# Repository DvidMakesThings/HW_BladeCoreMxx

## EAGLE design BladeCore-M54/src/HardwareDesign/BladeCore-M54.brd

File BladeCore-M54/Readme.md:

# BladeCore-M54

BladeCore-M54 is a versatile 6-layer embedded system module built around the RP2040 microcontroller, designed for modularity and high-speed experimentation in constrained spaces.  
It uses an M.2 form factor and includes a carefully routed, length-matched 16MB QSPI flash capable of operating at full 133 MHz quad I/O speeds — theoretically up to 532 Mbps effective throughput.  

The module provides optional breakouts for ADC, I²C, UART, GPIO, and USB signals — configurable based on application needs. Core voltage is externally adjustable via a trimpot-controlled LDO (AP7335-WG-7), enabling safe overclocking without risk of oversupply.  

USB routing is dynamically switchable using the PI3USB102J, allowing the single USB-C port to connect either to the MCU or to an FT232RNQ interface for debug automation.  
Boot/reset are handled programmatically; no physical boot/reset buttons are needed.  

It also includes:
- a high-precision 3.0 V analog reference supply (AVDD),
- a unique-ID EEPROM for per-module identification,
- and default configurations that favor RP2040-based development while leaving everything else adaptable.

BladeCore-M54 is not locked into any specific use case — it is meant to be reconfigured as needed.

---

## Highlights

- **RP2040 MCU** with external core voltage supply (AP7335-WG-7) for **safe overclocking** via trimpot  
- **16MB W25Q128JV QSPI Flash**, length-matched for up to **133 MHz quad I/O** (532 Mbps effective transfer rate)  
- **PI3USB102J USB switch**: 1 USB-C can switch between MCU and FT232RNQ (auto-debug, single cable)  
- Optional ADC, I²C, UART, and GPIO breakouts — **use what you need**  
- **No physical reset/boot buttons** — fully controllable by firmware  
- **3.0 V precision AVDD** generator for analog use  
- **External EEPROM with unique ID**  
- **Custom 6-layer JLC stackup**, tuned for signal integrity  
- **DMT signature layout** with aggressive routing and style

---

## Stackup

**JLC06081H-2116 (Finished Thickness: ~0.83 mm ±0.10 mm) – 6 Layers**

- Total Layers: 6  
- Finished Thickness: ~0.83 mm (±0.10 mm)  
- Outer Copper Weight: 1 oz  
- Inner Copper Weight: 0.5 oz  
- Prepreg & Core Materials: FR4 (JLC06081H-2116)

| Layer | Description     | Material                      | Thickness (mm) |
|-------|------------------|-------------------------------|----------------|
| L1    | Signal (Top)     | Outer Copper 1 oz             | 0.0350         |
|       | Prepreg          | 2116 RC54%, 4.9mil            | 0.1164         |
| L2    | Ground Plane     | Inner Copper 0.5 oz           | 0.0152         |
|       | Core             | 0.13 mm HOZ without copper    | 0.1300         |
| L3    | Power Plane      | Inner Copper 0.5 oz           | 0.0152         |
|       | Prepreg          | 7628 RC49%, 8.6mil            | 0.2028         |
| L4    | Signal           | Inner Copper 0.5 oz           | 0.0152         |
|       | Core             | 0.13 mm HOZ without copper    | 0.1300         |
| L5    | Ground Plane     | Inner Copper 0.5 oz           | 0.0152         |
|       | Prepreg          | 2116 RC54%, 4.9mil            | 0.1164         |
| L6    | Signal (Bottom)  | Outer Copper 1 oz             | 0.0350         |
|       |                  | **Total Thickness**           | **0.8304 mm**  |

---

## Pinout

| Pin | Signal      | Direction | Description |
|-----|-------------|-----------|-------------|
| 1   | GP15        | I/O       |             |
| 2   | GP29        | I/O       | ADC Channel 3 |
| 3   | GP14        | I/O       |             |
| 4   | GP28        | I/O       | ADC Channel 2 |
| 5   | GP13        | I/O       |             |
| 6   | GP27        | I/O       | ADC Channel 1 |
| 7   | GP12        | I/O       |             |
| 8   | GP26        | I/O       | ADC Channel 0 |
| 9   | GP11        | I/O       |             |
| 10  | GP25        | I/O       | USB MUX Select. For normal functionality, remove M1 and populate M3 (RP2040 USB) or M2 (FT232 USB). Default: M1 = 0Ω, M3 = 10K, M2 = DNI. |
| 11  | GP10        | I/O       |             |
| 12  | GP24        | I/O       |             |
| 13  | GP9         | I/O       | UART1 RX. Connected to FT232 via R01 (DNI). |
| 14  | GP23        | I/O       |             |
| 15  | GP8         | I/O       | UART1 TX. Connected to FT232 via T11 (DNI). |
| 16  | GP22        | I/O       |             |
| 17  | GP7         | I/O       |             |
| 18  | GP21        | I/O       |             |
| 19  | GP6         | I/O       |             |
| 20  | GP20        | I/O       |             |
| 21  | GP5         | I/O       | I2C0 SCL. Pulled high via R23 (3.3K). Remove R3 (0Ω) for non-I2C use. |
| 22  | GP19        | I/O       |             |
| 23  | GP4         | I/O       | I2C0 SDA. Pulled high via R24 (3.3K). Remove R4 (0Ω) for non-I2C use. |
| 24  | GP18        | I/O       |             |
| 25  | GP3         | I/O       |             |
| 26  | GP17        | I/O       |             |
| 27  | GP2         | I/O       |             |
| 28  | GP16        | I/O       |             |
| 29  | GP1         | I/O       | UART0 RX. Connected to FT232 via M1 (0Ω). |
| 30  | GND         | —         |             |
| 31  | GP0         | I/O       | UART0 TX. Connected to FT232 via T01 (0Ω). |
| 32  | NC          | —         | No functionality, used by BladeCore-M54. |
| 33  | GND         | —         |             |
| 34  | NC          | —         | No functionality, used by BladeCore-M54. |
| 35  | NC          | —         | No functionality, used by BladeCore-M54. |
| 36  | NC          | —         | No functionality, used by BladeCore-M54. |
| 37  | NC          | —         | No functionality, used by BladeCore-M54. |
| 38  | NC          | —         | No functionality, used by BladeCore-M54. |
| 39  | NC          | —         | No functionality, used by BladeCore-M54. |
| 40  | NC          | —         | No functionality, used by BladeCore-M54. |
| 41  | NC          | —         | No functionality, used by BladeCore-M54. |
| 42  | NC          | —         | No functionality, used by BladeCore-M54. |
| 43  | NC          | —         | No functionality, used by BladeCore-M54. |
| 44  | NC          | —         | No functionality, used by BladeCore-M54. |
| 45  | NC          | —         | No functionality, used by BladeCore-M54. |
| 46  | NC          | —         | No functionality, used by BladeCore-M54. |
| 47  | NC          | —         | No functionality, used by BladeCore-M54. |
| 48  | NC          | —         | No functionality, used by BladeCore-M54. |
| 49  | NC          | —         | No functionality, used by BladeCore-M54. |
| 50  | NC          | —         | No functionality, used by BladeCore-M54. |
| 51  | GND         | —         | System ground |
| 52  | GND         | —         | System ground |
| 53  | USB D+      | I/O       |             |
| 54  | RESET       | Input     |             |
| 55  | USB D-      | I/O       |             |
| 56  | SWDIO       | I/O       |             |
| 57  | DETECT      | -         | Pull low externally |
| 58  | SWCLK       | Input     |             |
| 67  | +3.3V       | PWR       | RP2040 supply voltage. Max 3.6V, typical 3.3V. |
| 68  | +3.3V       | PWR       |             |
| 69  | +3.3V       | PWR       |             |
| 70  | GND         | —         | System ground |
| 71  | GND         | —         | System ground |
| 72  | GND         | —         | System ground |
| 73  | VBUS        | PWR IN    | External power input. Max 5.5V. |
| 74  | VBUS        | PWR IN    | External power input. Max 5.5V. |
| 75  | VBUS        | PWR IN    | External power input. Max 5.5V. |

## Misc: Core Voltage & Overclocking

To overclock the MCU, it's possible to supply more than 1.1 V to the core.  
By default, **external core voltage generation** is enabled using the **AP7335-WG-7**, which is activated via **J1**.  
The output voltage is set by adjusting the **R1 trimpot**.

> ⚠️ It is safe — the voltage range is limited by design and cannot damage the MCU.

### Voltage Range (Set by Divider)

| R1 (Trimpot) | Total Resistance (R28 + R1) | VOUT (approx) |
|--------------|----------------------------|----------------|
| 25 kΩ (max)  | 47 kΩ                       | 1.02 V         |
| 12.5 kΩ      | 34.5 kΩ                     | 1.14 V         |
| 0 Ω (min)    | 22 kΩ                       | 1.22 V         |

### Use Cases

- **Low Power Mode:** R1 = 25 kΩ → ~1.02 V  
- **Default / Safe:** R1 = 12.5 kΩ → ~1.14 V  
- **High Performance / Overclocking:** R1 = 0 Ω → ~1.22 V  

### VOUT Behavior Across Temperatures and Trim Settings

The AP7335-WG-7 regulator is affected by temperature-dependent reference voltage (VREF), output voltage accuracy, and resistor tolerances.  
This section outlines the **worst-case VOUT values** at cold, normal, and hot temperatures, across all trimpot settings.

> ⚙️ **Calculation Parameters:**
> - VOUT Accuracy: ±2% (from AP7335-WG-7 datasheet)
> - VREF Variation: Based on VREF vs. Temperature graph  
>   - −50 °C → 0.89 V  
>   - 25 °C → 0.80 V  
>   - 125 °C → 0.782 V
> - Resistors used: 1% tolerance (R27 = 12 kΩ, R28 = 22 kΩ, R1 = 0–25 kΩ trimpot)

The RP2040's **absolute maximum core voltage is 1.3 V** — values exceeding this may cause damage.

---

### ❄️ Cold (–50 °C, VREF = 0.89 V)

**Max Trim (R1 = 25 kΩ, Rb = 47 kΩ)**  
VOUT: **1.090 V – 1.144 V** ✅ Safe

**Mid Trim (R1 = 12.5 kΩ, Rb = 34.5 kΩ)**  
VOUT: **1.170 V – 1.230 V** ✅ Safe

**Min Trim (R1 = 0 Ω, Rb = 22 kΩ)**  
VOUT: **1.339 V – 1.413 V** ❌ Danger – exceeds RP2040 1.3 V limit

---

### 🌤️ Normal (25 °C, VREF = 0.80 V)

**Max Trim (R1 = 25 kΩ, Rb = 47 kΩ)**  
VOUT: **0.980 V – 1.029 V** ✅ Safe

**Mid Trim (R1 = 12.5 kΩ, Rb = 34.5 kΩ)**  
VOUT: **1.051 V – 1.106 V** ✅ Safe

**Min Trim (R1 = 0 Ω, Rb = 22 kΩ)**  
VOUT: **1.201 V – 1.265 V** ✅ Safe

---

### 🔥 Hot (125 °C, VREF = 0.782 V)

**Max Trim (R1 = 25 kΩ, Rb = 47 kΩ)**  
VOUT: **0.958 V – 1.005 V** ✅ Safe

**Mid Trim (R1 = 12.5 kΩ, Rb = 34.5 kΩ)**  
VOUT: **1.028 V – 1.082 V** ✅ Safe

**Min Trim (R1 = 0 Ω, Rb = 22 kΩ)**  
VOUT: **1.180 V – 1.243 V** ✅ Safe

### Switching to Internal Core LDO

To use the **internally generated core voltage** (from RP2040's internal LDO):

1. Move **J1 → J2**  
2. Populate **J3** with a 0 Ω jumper  

**Default configuration:**
- J1 = 10 kΩ  
- J2 = DNI  
- J3 = DNI

---
## License
This project is licensed under the GPL-3.0 License. See the [LICENSE](LICENSE) file for details.

## Contact
For questions or feedback:
- Email: [dvidmakesthing@gmail.com](mailto:dvidmakesthing@gmail.com)
- GitHub: [DvidMakesThings](https://github.com/DvidMakesThings)

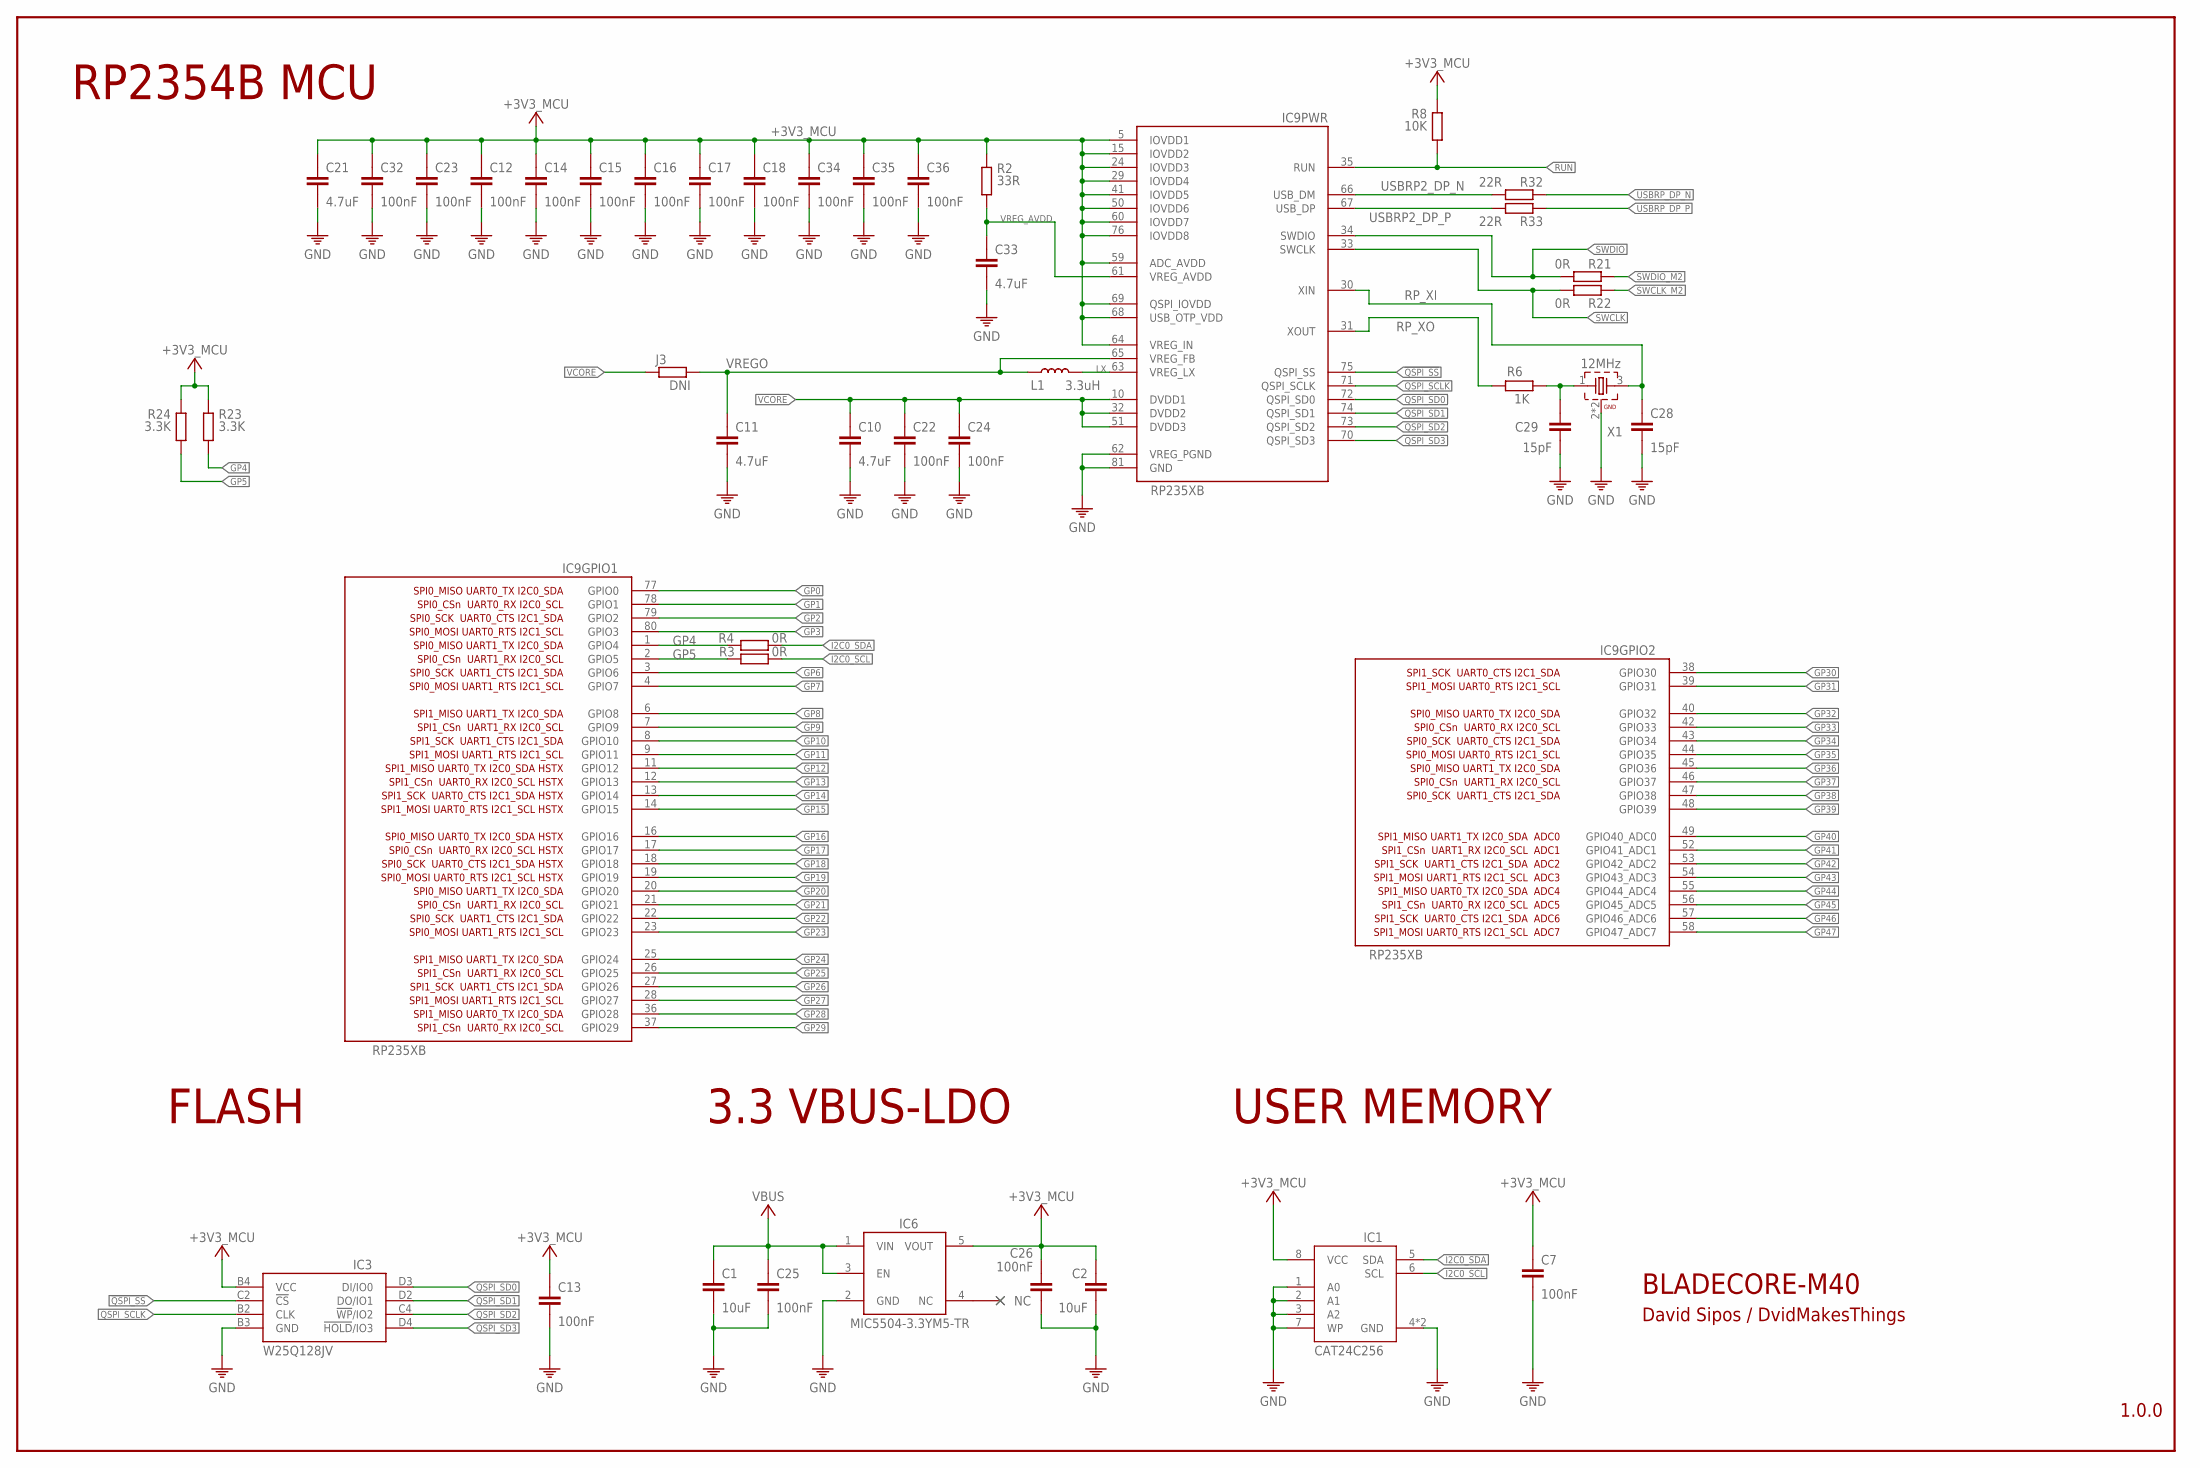
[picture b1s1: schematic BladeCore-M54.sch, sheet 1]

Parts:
C1, C2: 10uF; 0805
C7, C12, C13, C14, C15, C16, C17, C18, C22, C23, C24, C25, C26, C32, C34, C35, C36: 100nF; 0201
C10, C11, C33: 4.7uF; 0201
C21: 4.7uF; C0402
C28, C29: 15pF; 0201
IC1: CAT24C512HU5IGT3; SON50P300X200X50-9T130X140N
IC3: W25Q128JVCIQ TR; BGA24C100P4X6_800X600X120N
IC6: MIC5504-3.3YM5-TR; SOT23-5
IC9: RP235XB; QFN80-10X10
J3: DNI; R0201
L1: 3.3uH; SRR5228A
R2: 33R; R0201
R3, R4, R21, R22: 0R; R0201
R6: 1K; R0201
R8: 10K; R0201
R23, R24: 3.3K; R0201
R32, R33: 22R; R0201
X1: 12MHz; WE-XTAL_CFPX-180

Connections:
!QSPI_SS: IC3.C2 (!CS), IC9.75 (QSPI_SS)
+3V3_MCU: C2.1, C7.1, C12.1, C13.1, C14.1, C15.1, C16.1, C17.1, C18.1, C21.1, C23.1, C26.1, C32.1, C34.1, C35.1, C36.1, IC1.8 (VCC), IC3.B4 (VCC), IC6.5 (VOUT), IC9.5 (IOVDD1), IC9.15 (IOVDD2), IC9.24 (IOVDD3), IC9.29 (IOVDD4), IC9.41 (IOVDD5), IC9.50 (IOVDD6), IC9.59 (ADC_AVDD), IC9.60 (IOVDD7), IC9.64 (VREG_IN), IC9.68 (USB_OTP_VDD), IC9.69 (QSPI_IOVDD), IC9.76 (IOVDD8), R2.1, R8.1, R23.1, R24.1; also elsewhere on the board
GND: C1.2, C2.2, C7.2, C10.2, C11.2, C12.2, C13.2, C14.2, C15.2, C16.2, C17.2, C18.2, C21.2, C22.2, C23.2, C24.2, C25.2, C26.2, C28.2, C29.2, C32.2, C33.2, C34.2, C35.2, C36.2, IC1.1 (A0), IC1.2 (A1), IC1.3 (A2), IC1.4 (GND), IC1.7 (WP), IC1.9 (GND), IC3.B3 (GND), IC6.2 (GND), IC9.62 (VREG_PGND), IC9.81 (GND), X1.2 (GND), X1.4 (GND); also elsewhere on the board
GP0: IC9.77 (GPIO0); also elsewhere on the board
GP1: IC9.78 (GPIO1); also elsewhere on the board
GP2: IC9.79 (GPIO2); also elsewhere on the board
GP3: IC9.80 (GPIO3); also elsewhere on the board
GP4: IC9.1 (GPIO4), R4.1, R23.2; also elsewhere on the board
GP5: IC9.2 (GPIO5), R3.1, R24.2; also elsewhere on the board
GP6: IC9.3 (GPIO6); also elsewhere on the board
GP7: IC9.4 (GPIO7); also elsewhere on the board
GP8: IC9.6 (GPIO8); also elsewhere on the board
GP9: IC9.7 (GPIO9); also elsewhere on the board
GP10: IC9.8 (GPIO10); also elsewhere on the board
GP11: IC9.9 (GPIO11); also elsewhere on the board
GP12: IC9.11 (GPIO12); also elsewhere on the board
GP13: IC9.12 (GPIO13); also elsewhere on the board
GP14: IC9.13 (GPIO14); also elsewhere on the board
GP15: IC9.14 (GPIO15); also elsewhere on the board
GP16: IC9.16 (GPIO16); also elsewhere on the board
GP17: IC9.17 (GPIO17); also elsewhere on the board
GP18: IC9.18 (GPIO18); also elsewhere on the board
GP19: IC9.19 (GPIO19); also elsewhere on the board
GP20: IC9.20 (GPIO20); also elsewhere on the board
GP21: IC9.21 (GPIO21); also elsewhere on the board
GP22: IC9.22 (GPIO22); also elsewhere on the board
GP23: IC9.23 (GPIO23); also elsewhere on the board
GP24: IC9.25 (GPIO24); also elsewhere on the board
GP25: IC9.26 (GPIO25); also elsewhere on the board
GP26: IC9.27 (GPIO26); also elsewhere on the board
GP27: IC9.28 (GPIO27); also elsewhere on the board
GP28: IC9.36 (GPIO28); also elsewhere on the board
GP29: IC9.37 (GPIO29); also elsewhere on the board
GP30: IC9.38 (GPIO30); also elsewhere on the board
GP31: IC9.39 (GPIO31); also elsewhere on the board
GP32: IC9.40 (GPIO32); also elsewhere on the board
GP33: IC9.42 (GPIO33); also elsewhere on the board
GP34: IC9.43 (GPIO34); also elsewhere on the board
GP35: IC9.44 (GPIO35); also elsewhere on the board
GP36: IC9.45 (GPIO36); also elsewhere on the board
GP37: IC9.46 (GPIO37); also elsewhere on the board
GP38: IC9.47 (GPIO38); also elsewhere on the board
GP39: IC9.48 (GPIO39); also elsewhere on the board
GP40: IC9.49 (GPIO40_ADC0); also elsewhere on the board
GP41: IC9.52 (GPIO41_ADC1); also elsewhere on the board
GP42: IC9.53 (GPIO42_ADC2); also elsewhere on the board
GP43: IC9.54 (GPIO43_ADC3); also elsewhere on the board
GP44: IC9.55 (GPIO44_ADC4); also elsewhere on the board
GP45: IC9.56 (GPIO45_ADC5); also elsewhere on the board
GP46: IC9.57 (GPIO46_ADC6); also elsewhere on the board
GP47: IC9.58 (GPIO47_ADC7); also elsewhere on the board
I2C0_SCL: IC1.6 (SCL), R3.2
I2C0_SDA: IC1.5 (SDA), R4.2
LX: IC9.63 (VREG_LX), L1.2
unnamed: C29.1, R6.1, X1.1
QSPI_SCLK: IC3.B2 (CLK), IC9.71 (QSPI_SCLK)
QSPI_SD0: IC3.D3 (DI/IO0), IC9.72 (QSPI_SD0)
QSPI_SD1: IC3.D2 (DO/IO1), IC9.74 (QSPI_SD1)
QSPI_SD2: IC3.C4 (!WP!/IO2), IC9.73 (QSPI_SD2)
QSPI_SD3: IC3.D4 (!HOLD!/IO3), IC9.70 (QSPI_SD3)
RP_XI: C28.1, IC9.30 (XIN), X1.3 (2)
RP_XO: IC9.31 (XOUT), R6.2
RUN: IC9.35 (RUN), R8.2; also elsewhere on the board
SWCLK: IC9.33 (SWCLK), R22.2
SWCLK_M2: R22.1; also elsewhere on the board
SWDIO: IC9.34 (SWDIO), R21.2
SWDIO_M2: R21.1; also elsewhere on the board
USBRP2_DP_N: IC9.66 (USB_DM), R32.2
USBRP2_DP_P: IC9.67 (USB_DP), R33.2
USBRP_DP_N: R32.1; also elsewhere on the board
USBRP_DP_P: R33.1; also elsewhere on the board
VBUS: C1.1, C25.1, IC6.1 (VIN), IC6.3 (EN); also elsewhere on the board
VCORE: C10.1, C22.1, C24.1, IC9.10 (DVDD1), IC9.32 (DVDD2), IC9.51 (DVDD3), J3.2
VREGO: C11.1, IC9.65 (VREG_FB), J3.1, L1.1
VREG_AVDD: C33.1, IC9.61 (VREG_AVDD), R2.2

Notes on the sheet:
RP2354B MCU
BLADECORE-M40
1.0.0
David Sipos / DvidMakesThings
3.3 VBUS-LDO
FLASH
USER MEMORY

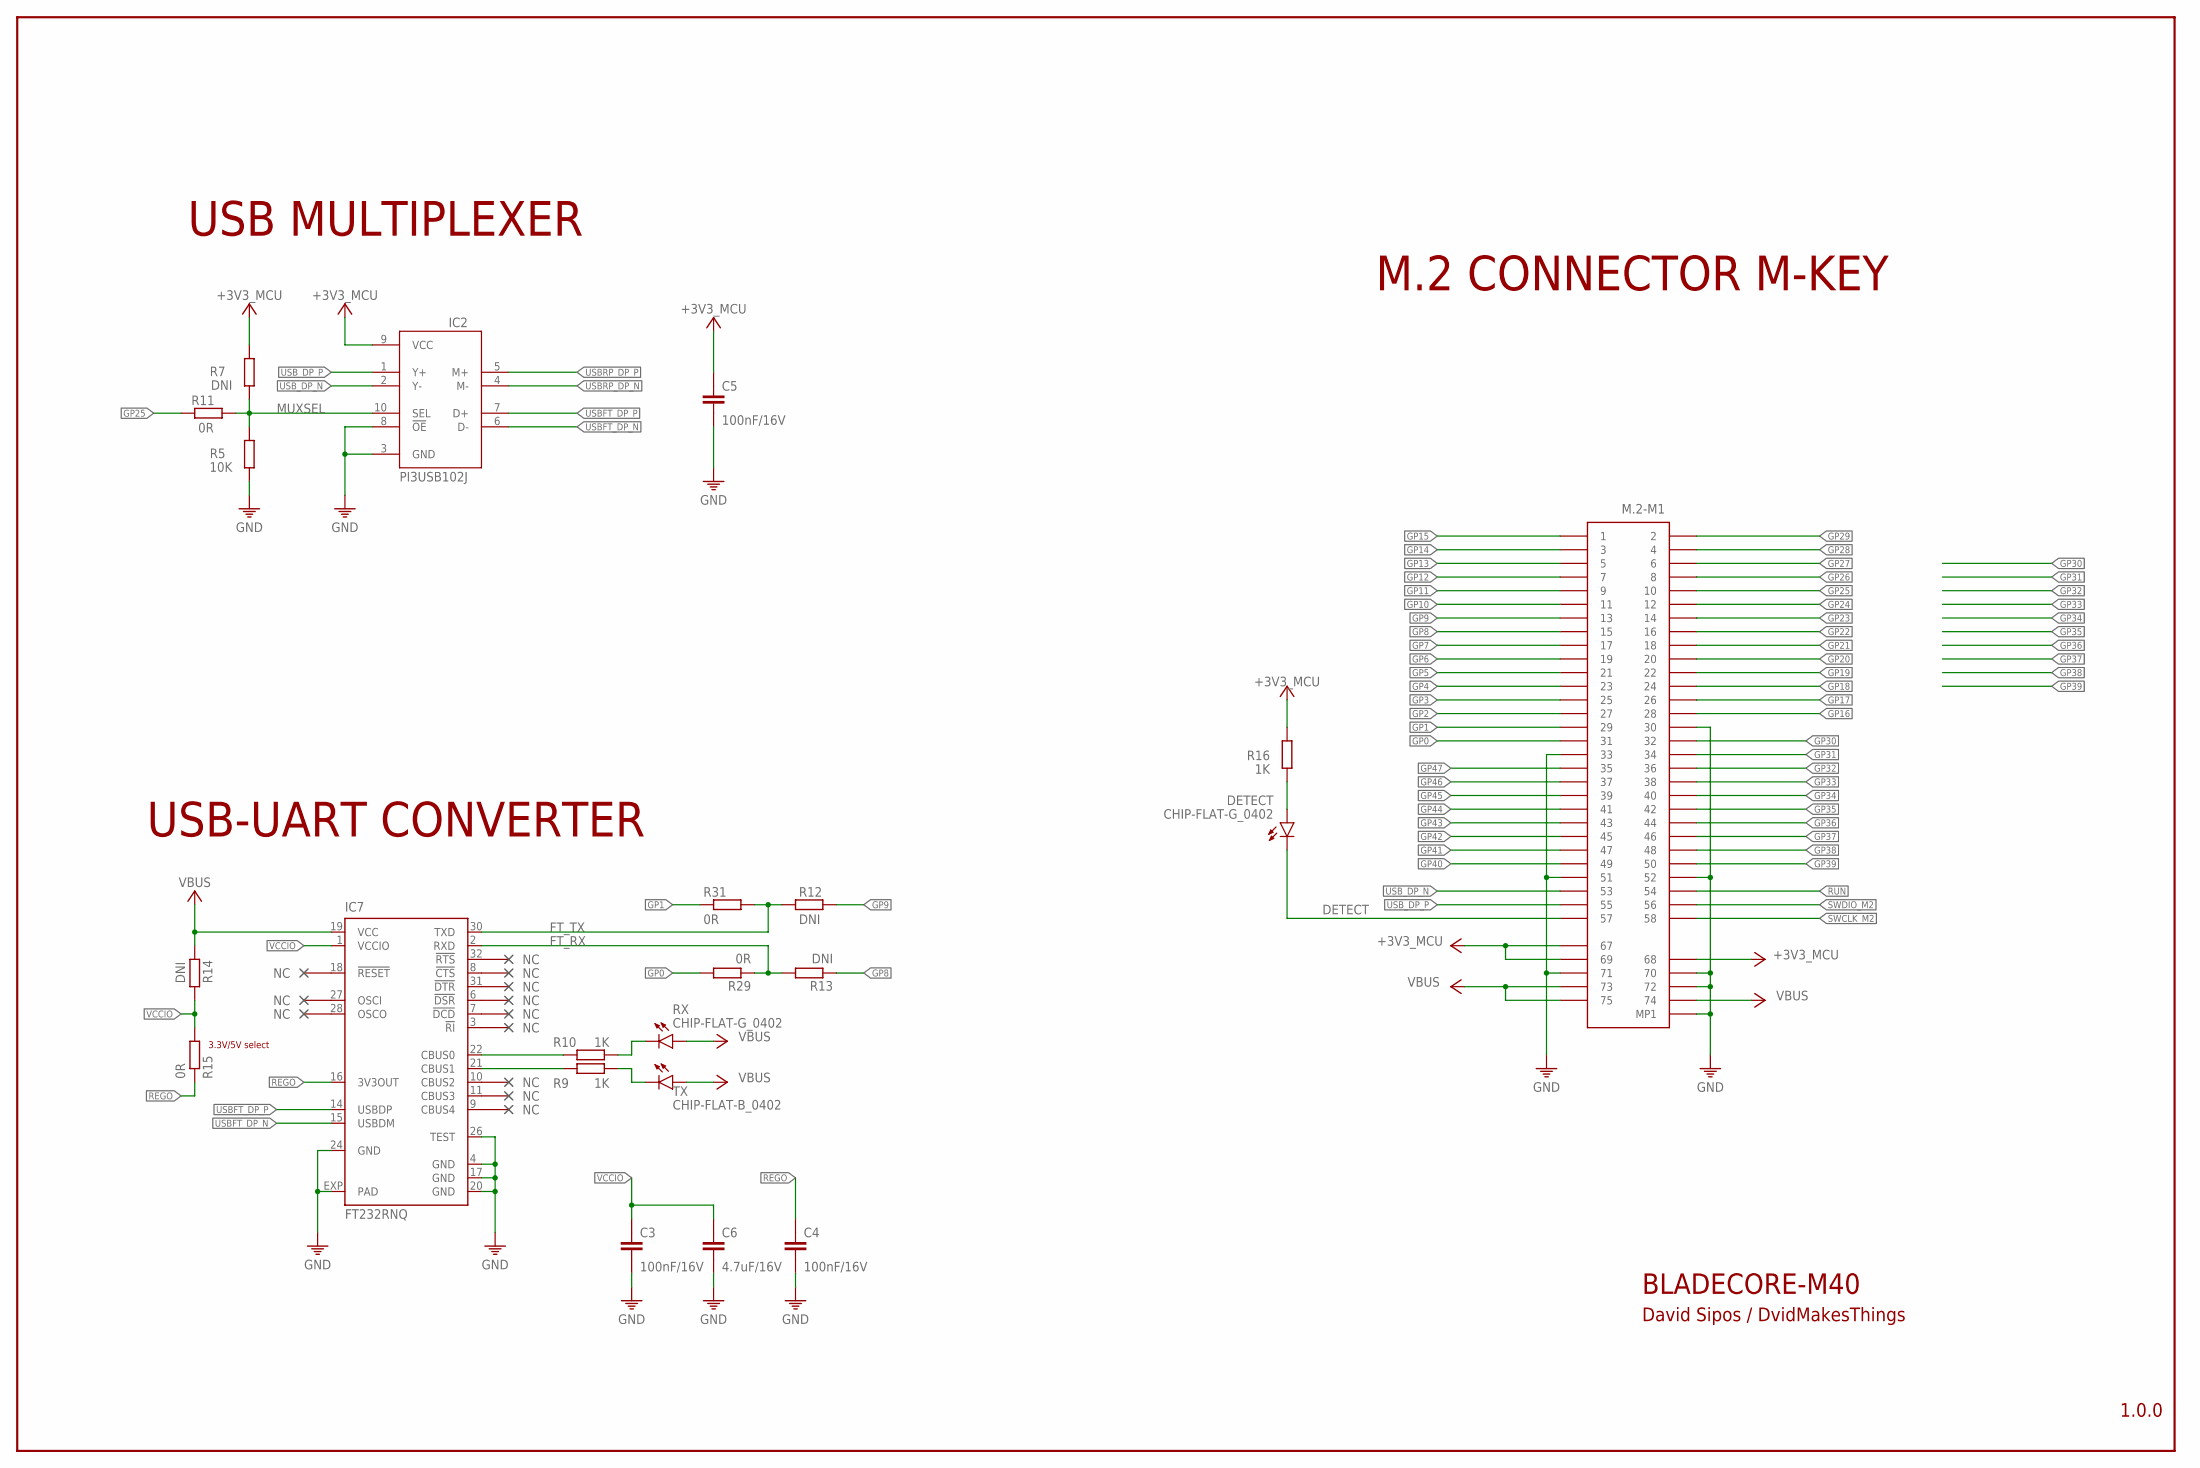
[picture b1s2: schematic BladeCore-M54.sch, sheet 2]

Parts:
C3, C4, C5: 100nF/16V; 0201
C6: 4.7uF/16V; 0201
DETECT: CHIP-FLAT-G_0402; LEDC1005X25N_FLAT-G
IC2: PI3USB102J; QFN40P120X140X35-10N
IC7: FT232RNQ; QFN32
M.2-M1: M.2-M-KEY
R5: 10K; R0201
R7, R12, R13, R14: DNI; R0201
R9, R10, R16: 1K; R0201
R11, R15, R29, R31: 0R; R0201
RX: CHIP-FLAT-G_0402; LEDC1005X25N_FLAT-G
TX: CHIP-FLAT-B_0402; LEDC1005X25N_FLAT-B

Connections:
+3V3_MCU: C5.1, IC2.9 (VCC), M.2-M1.P$67 (67), M.2-M1.P$68 (68), M.2-M1.P$69 (69), R7.2, R16.2; also elsewhere on the board
DETECT: DETECT.C, M.2-M1.P$57 (57)
FT_RX: IC7.2 (RXD), R13.2, R29.1
FT_TX: IC7.30 (TXD), R12.1, R31.2
GND: C3.2, C4.2, C5.2, C6.2, IC2.3 (GND), IC2.8 (!OE), IC7.4 (GND), IC7.17 (GND), IC7.20 (GND), IC7.24 (GND), IC7.26 (TEST), IC7.EXP (PAD), M.2-M1.MT1 (MP1), M.2-M1.P$30 (30), M.2-M1.P$33 (33), M.2-M1.P$51 (51), M.2-M1.P$52 (52), M.2-M1.P$70 (70), M.2-M1.P$71 (71), M.2-M1.P$72 (72), R5.1; also elsewhere on the board
GP0: M.2-M1.P$31 (31), R29.2; also elsewhere on the board
GP1: M.2-M1.P$29 (29), R31.1; also elsewhere on the board
GP2: M.2-M1.P$27 (27); also elsewhere on the board
GP3: M.2-M1.P$25 (25); also elsewhere on the board
GP4: M.2-M1.P$23 (23); also elsewhere on the board
GP5: M.2-M1.P$21 (21); also elsewhere on the board
GP6: M.2-M1.P$19 (19); also elsewhere on the board
GP7: M.2-M1.P$17 (17); also elsewhere on the board
GP8: M.2-M1.P$15 (15), R13.1; also elsewhere on the board
GP9: M.2-M1.P$13 (13), R12.2; also elsewhere on the board
GP10: M.2-M1.P$11 (11); also elsewhere on the board
GP11: M.2-M1.P$9 (9); also elsewhere on the board
GP12: M.2-M1.P$7 (7); also elsewhere on the board
GP13: M.2-M1.P$5 (5); also elsewhere on the board
GP14: M.2-M1.P$3 (3); also elsewhere on the board
GP15: M.2-M1.P$1 (1); also elsewhere on the board
GP16: M.2-M1.P$28 (28); also elsewhere on the board
GP17: M.2-M1.P$26 (26); also elsewhere on the board
GP18: M.2-M1.P$24 (24); also elsewhere on the board
GP19: M.2-M1.P$22 (22); also elsewhere on the board
GP20: M.2-M1.P$20 (20); also elsewhere on the board
GP21: M.2-M1.P$18 (18); also elsewhere on the board
GP22: M.2-M1.P$16 (16); also elsewhere on the board
GP23: M.2-M1.P$14 (14); also elsewhere on the board
GP24: M.2-M1.P$12 (12); also elsewhere on the board
GP25: M.2-M1.P$10 (10), R11.2; also elsewhere on the board
GP26: M.2-M1.P$8 (8); also elsewhere on the board
GP27: M.2-M1.P$6 (6); also elsewhere on the board
GP28: M.2-M1.P$4 (4); also elsewhere on the board
GP29: M.2-M1.P$2 (2); also elsewhere on the board
GP30: M.2-M1.P$32 (32); also elsewhere on the board
GP31: M.2-M1.P$34 (34); also elsewhere on the board
GP32: M.2-M1.P$36 (36); also elsewhere on the board
GP33: M.2-M1.P$38 (38); also elsewhere on the board
GP34: M.2-M1.P$40 (40); also elsewhere on the board
GP35: M.2-M1.P$42 (42); also elsewhere on the board
GP36: M.2-M1.P$44 (44); also elsewhere on the board
GP37: M.2-M1.P$46 (46); also elsewhere on the board
GP38: M.2-M1.P$48 (48); also elsewhere on the board
GP39: M.2-M1.P$50 (50); also elsewhere on the board
GP40: M.2-M1.P$49 (49); also elsewhere on the board
GP41: M.2-M1.P$47 (47); also elsewhere on the board
GP42: M.2-M1.P$45 (45); also elsewhere on the board
GP43: M.2-M1.P$43 (43); also elsewhere on the board
GP44: M.2-M1.P$41 (41); also elsewhere on the board
GP45: M.2-M1.P$39 (39); also elsewhere on the board
GP46: M.2-M1.P$37 (37); also elsewhere on the board
GP47: M.2-M1.P$35 (35); also elsewhere on the board
MUXSEL: IC2.10 (SEL), R5.2, R7.1, R11.1
unnamed: DETECT.A, R16.1
unnamed: IC7.22 (CBUS0), R10.1
unnamed: IC7.21 (CBUS1), R9.1
unnamed: R9.2, TX.C
unnamed: R10.2, RX.C
REGO: C4.1, IC7.16 (3V3OUT), R15.1
RUN: M.2-M1.P$54 (54); also elsewhere on the board
SWCLK_M2: M.2-M1.P$58 (58); also elsewhere on the board
SWDIO_M2: M.2-M1.P$56 (56); also elsewhere on the board
USBFT_DP_N: IC2.6 (D-), IC7.15 (USBDM)
USBFT_DP_P: IC2.7 (D+), IC7.14 (USBDP)
USBRP_DP_N: IC2.4 (M-); also elsewhere on the board
USBRP_DP_P: IC2.5 (M+); also elsewhere on the board
USB_DP_N: IC2.2 (Y-), M.2-M1.P$53 (53)
USB_DP_P: IC2.1 (Y+), M.2-M1.P$55 (55)
VBUS: IC7.19 (VCC), M.2-M1.P$73 (73), M.2-M1.P$74 (74), M.2-M1.P$75 (75), R14.2, RX.A, TX.A; also elsewhere on the board
VCCIO: C3.1, C6.1, IC7.1 (VCCIO), R14.1, R15.2

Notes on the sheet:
3.3V/5V select
USB MULTIPLEXER
USB-UART CONVERTER
M.2 CONNECTOR M-KEY
BLADECORE-M40
1.0.0
David Sipos / DvidMakesThings

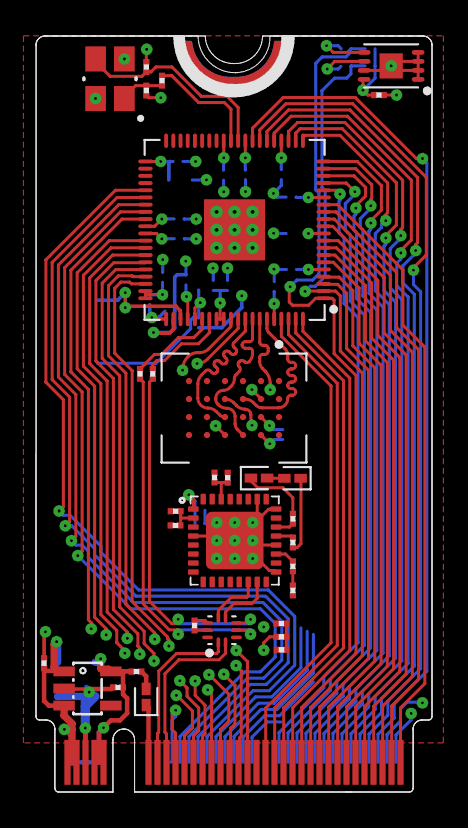
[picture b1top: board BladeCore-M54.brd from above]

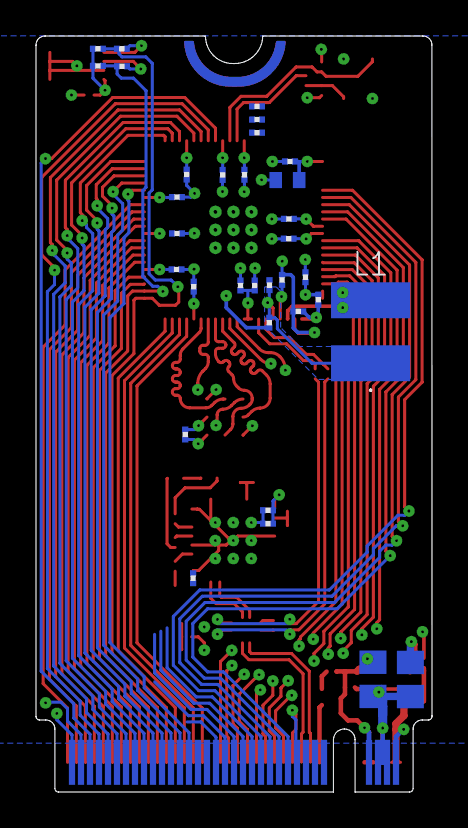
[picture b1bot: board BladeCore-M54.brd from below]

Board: 6 copper layers, 22.0 x 42.0 mm, 66 parts (34 on the bottom side), 90 nets.

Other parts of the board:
U$1: DMT

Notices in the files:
BladeCore-M40/Readme.md:
License:
This project is licensed under the GPL-3.0 License. See the [LICENSE](LICENSE) file for details.
parts and their libraries:
Wurth_Quartz Crystals: Copyright: Würth Elektronik
